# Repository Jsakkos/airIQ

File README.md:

# airQ

Open-source indoor air-quality monitor: ESP32-C6 + Sensirion SEN66 (PM, CO2, VOC, NOx, temperature, humidity), e-paper display, RGB status LED, ESPHome firmware, KiCad PCB and a 3D-printed enclosure.

**Status:** v3 is in design and early implementation.

- Design spec: [docs/superpowers/specs/2026-11-25-airq-v3-design.md](docs/superpowers/specs/2026-11-25-airq-v3-design.md)
- Implementation plans: [docs/superpowers/plans/](docs/superpowers/plans/)
- Research report: [docs/research/reports/Air quality monitor refresh.md](docs/research/reports/Air%20quality%20monitor%20refresh.md)
- Hardware interface contract (GPIOs, I2C addresses, connector pinouts): [hardware/interface.yaml](hardware/interface.yaml)
- Previous generation (v2, ESP8266): [legacy/v2/](legacy/v2/README.md)

## Licences

- `firmware/` and `tools/`: [MIT](LICENSE)
- `hardware/` and `enclosure/`: [CC-BY-SA 4.0](hardware/LICENSE.md)

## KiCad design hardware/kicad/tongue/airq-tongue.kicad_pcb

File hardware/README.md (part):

# airQ v3 hardware

| Path | What |
|---|---|
| `src/<board>/` | **Design source**: the text files the boards are made from (edit these) |
| `kicad/<board>/` | KiCad 10 projects, **generated** from `src/<board>/` (open these, do not edit the schematics) |
| `kicad/lib/` | `airq` symbol, footprint and 3D library ([README](kicad/lib/README.md)) |
| `fab/<board>/` | **JLCPCB upload files**, generated by every build: Gerber + drill zip, `bom.csv`, `cpl.csv` (see "Ordering") |
| `step/` | STEP models of both assembled boards for the enclosure, from `build.py <board> --step` |
| `bom/parts.csv` | LCSC parts table: JLC Economic status, stock, boards |
| `interface.yaml` | GPIOs, I²C addresses and connector pinouts shared with the firmware; board mechanics (`mechanical`) |

Boards: `main` (the main board) and `tongue` (the sense tongue: SHT45 and VEML7700 on a 22 × 13 mm
board cabled to the main board's `J_QWIIC_TONGUE`, see below). Both follow the same scheme.

## Ordering

Both boards are ordered from JLCPCB as PCB + assembly (PCBA). The owner places the orders; nothing in
this repository uploads or orders anything.

**Files to upload, per board** (in `hardware/fab/main/` and `hardware/fab/tongue/`; every build rewrites
them and a test fails if the committed ones differ from a rebuild, see "Fab outputs"):

| File | JLC upload slot | Contents |
|---|---|---|
| `airq-<board>-gerbers.zip` | Gerber file (PCB) | 9 Gerber layers (copper, paste, silkscreen and mask, top and bottom; the outline with the tongue's slot) and the PTH and NPTH Excellon drill files |
| `bom.csv` | BOM (assembly) | `Comment,Designator,Footprint,LCSC`, one line per part kind; DNP parts left out |
| `cpl.csv` | CPL / pick-and-place (assembly) | `Designator,Mid X,Mid Y,Layer,Rotation`, mm from the outline's bottom-left corner, all `Top` |

**JLC options**, the same for both boards:

- PCB: **2 layers, 1.6 mm, lead-free HASL** (FR-4, 1 oz copper). Colour and the rest are the owner's choice.
- Assembly: **Economic** PCBA, top side. The main board has 28 BOM lines, 14 of them Extended parts (≤ 15,
  the fee budget); the tongue 4 lines, 3 Extended. The parts are the owner-confirmed set (2026-11-25):
  ESP32-C6-WROOM-1-N8 (C5366877) and MS5611 (C15639), both Economic-eligible.
- **Prototype round:** fabricate **5**, assemble **2** of each board.
- **Production:** fabricate **10**, assemble **8** of each board.

**Before each order:**

1. Rebuild both boards (`build.py main --routed`, `build.py tongue --routed`: exit 0, DRC clean), run the
   gates and the tests ("Build and check a board" below), and check that `git status` is clean, so the files
   you upload are what was checked. This holds on KiCad 10.0.8, the pinned release: on any other, the
   rebuild rewrites the files KiCad saves (see "Regeneration contract"); check and commit that rebuild first.
2. On the day of the order, look up every BOM part on LCSC/JLC (stock, still "Economic"), update `stock` and
   `checked_on` in `bom/parts.csv`, then run the freshness gate. It must print nothing (exit 0):
   ```
   uv run python tools/hw/check_bom.py hardware/fab/main/bom.csv hardware/bom/parts.csv --fresh-days 7
   uv run python tools/hw/check_bom.py hardware/fab/tongue/bom.csv hardware/bom/parts.csv --fresh-days 7
   ```
   Watch the VEML7700-TR (C504893, tongue): only 308 were in stock on 2026-11-25.
3. **Main boards meant for airQs: test the e-ink extension first.** In the airQ the panel's tail does not
   reach J7, so it connects through a 24-pin adapter and FFC (owner decision 2026-11-26, "E-ink FPC fit
   (airQ)" below). Before ordering main boards for airQs beyond the prototype round, run one prototype airQ
   with the real adapter and FFC: check with a meter, before power, that FPC pin 1 reaches J7 pin 1, then
   confirm full and partial refreshes are clean with the panel's boost (GDR, RESE) running through the
   extension. If either fails, the options in that section are open again. Boards for the bench or the
   airQ mini are not affected.
4. **Side-looking parts, if one of each is at hand:** check against the real part that the SK6812SIDE-A
   emits from the face opposite its terminals (footprint +y, out of the main board's front edge) and that the
   VEML7700-TR's window is on the side opposite its leads (footprint −y, out of the tongue's front edge).
   Both directions were read from 2-D drawings only (`kicad/lib/README.md`, "Pad maps checked by hand", fix 13).
5. After uploading, **look at the files in JLC's Gerber viewer** (every copper, mask, paste and silkscreen
   layer; the outline with the tongue's slot; the drill holes, including the USB-C shell-leg slots and their
   paste) **and check its rotation/offset preview against the silkscreen before paying**: every
   part's pin 1 or polarity mark (D5–D7 cathode bars, the SOT-23 parts U1, U2, U5, Q1, the module U3, U4, and
   the tongue's U1), and the parts that look out of a board edge (LEDs D1–D4, J1–J5, the FPC J7, the button
   SW1, the tongue's VEML7700 U2 and J1) facing out of that edge as the silkscreen shows. The CPL uses
   KiCad's rotations with no per-part offsets (see "Fab outputs"); correct any part JLC shows turned in its
   preview, and note it here for the next order. No Gerber viewer was run on these files before the first
   order; KiCad's own checks and `tests/hardware/test_fab.py` are all that has read them.

**Bought separately** (not on JLC's BOM): 11 SEN66, SEN6x cables (JST GH 6-pin), e-ink panels (GoodDisplay
GDEY029T94), Qwiic cables (JST SH 4-pin, also for the tongue), and the optional SFA40. For each airQ (the
mini needs neither): a 24-pin 0.5 mm FPC adapter and a 24-pin 0.5 mm-pitch FFC for the panel, the FFC's
length and contact sides set by Plan 3's route ("E-ink FPC fit (airQ)" below).

**USB supply and cable** (not part of the BOM, spec §6.7): a 5 V supply good for 1 A and a decent cable. The
TPS562201 buck is specified for VIN ≥ 4.5 V (its undervoltage lockout wakes at 3.8–4.3 V), and the LED buffer
(SN74AHCT1G125, VCC 4.5–5.5 V) runs on +5 V too. A long or thin cable that lets VBUS sag at about 1 A can brown
the board out (ruling R29).

**Not fitted:** J6 (`J_AUX_UART`, DNP): JLC drills and plates its six 2.54 mm holes and fits no header.

**Design rules against JLC's published capabilities** (jlcpcb.com/capabilities/pcb-capabilities and
/pcb-assembly-capabilities, read 2026-11-25; measured with KiCad DRC on both boards):

| Feature | These boards | JLC |
|---|---|---|
| Tongue slot round the SHT45 | 1.0 mm wide, drawn on Edge.Cuts (the GM1 file) | "Min. Non-Plated Slots: 1.0mm", outline in GM1/GKO: **at the minimum, no margin**. JLC may query its square corners ("rectangular holes and slots without rounded corners are not supported"): the router bit rounds them, which is fine here |
| Copper to non-plated holes (M2 holes, SW1 guide holes, USB-C pegs) | ≥ 0.25 mm (SW1 and USB-C pads trimmed, no relaxing DRC rule: `kicad/lib/README.md` fixes 18, 19) | "NPTH to Track: 0.2mm" |
| Copper to plated holes (J6, USB-C shell legs) | ≥ 0.4 mm | "PTH to Track": 0.28 mm minimum, 0.35 mm recommended |
| Annular ring of plated holes | J6 0.35 mm, USB-C shell legs ≥ 0.25 mm | ≥ 0.18 mm absolute minimum, 0.25 mm recommended |
| Vias | 0.6 mm on 0.3 mm; ≥ 0.30 mm from the hole to other copper | 0.25 mm on 0.15 mm minimum; "Via hole to Track: 0.2mm" |
| Track width / clearance | ≥ 0.15 / 0.15 mm | 0.10 / 0.10 mm (1 oz) |
| Copper to the board edge and to the slot | ≥ 0.3 mm | ≥ 0.2 mm from routed edges and slots |
| Board size, assembly | 60 × 30 mm, 22 × 13 mm | Economic PCBA: 10 × 10 mm minimum, one side, 2–50 boards, edge rails and fiducials "not necessary" |
| Silkscreen | text 1.0 mm high, 0.15 mm stroke; some footprint outlines 0.06–0.12 mm (KiCad stock and EasyEDA footprints) | line width ≥ 0.15 mm, text ≥ 1.0 mm high: the thinner outline lines may print faint (cosmetic) |

**Parts at the board edges** (for JLC's question about edge rails, a panel or tabs; Economic PCBA lists edge
rails as not necessary, so adding them is an owner decision on cost). Positions from `interface.yaml`
`mechanical.*`:

| Edge | Parts at or over it |
|---|---|
| Main, rear (y = 0) | the module U3's 6 mm antenna strip **overhangs** it (x 41–59); the USB-C J1's mouth is flush (y 0.03, x 11.7–20.7) |
| Main, front (y = 30) | the LEDs D1–D4 (light faces on the edge), the FPC J7's mouth (on the edge, x 21–36.5), the button SW1's actuator **0.24 mm beyond** it (x 56–58), the J3 and J5 mouths 0.6 and 0.8 mm inside |
| Main, left (x = 0) | the J2 (SEN66) and J4 (Qwiic) mouths, 0.35 and 0.64 mm inside |
| Main, right (x = 60) | nothing; the module body ends 1 mm inside |
| Tongue, front (y = 0) | the VEML7700 U2's window face, 0.25 mm inside (x 14.95–21.75) |
| Tongue, rear (y = 13) | the Qwiic J1's mouth, 0.64 mm inside (x 12–18) |

So the main board's right edge is the only one free of parts, and the only one a rail or V-groove could run
along without touching a part (the module ends 1 mm from it). On the other three edges the parts need their
edge clear: a routed outline with tabs placed away from them, and nothing at all in front of the antenna
strip. On the tongue, keep rails and tabs off the front and rear edges.

The USB-C receptacle J1's four plated shell legs have pin-in-paste apertures on F.Paste, sized to their pads
(`kicad/lib/README.md` fix 22), and reach the pours through thermal reliefs (only its SMD ground pins are
tied solid), so they solder in JLC's SMT reflow with the rest of the part. Still confirm in JLC's review that
the legs get soldered.

### E-ink FPC fit (airQ): decided, extension (option b)

**Decision** (owner, 2026-11-26): option (b) below. A 24-pin 0.5 mm adapter at the panel's tail end takes
the tail, and a 24-pin 0.5 mm FFC runs from it to J7 as placed. **No board change.** In the airQ the tail
folds behind the panel into the adapter. Before ordering airQ boards beyond the prototype round, one
prototype must show the panel's boost (GDR, RESE) working through the extension, and pin 1 arriving on J7
pin 1 (step 3 of "Before each order"). Recorded in `interface.yaml` `mechanical.main.fpc.airq_fit`. The
analysis behind it follows.

**The panel's tail**, read from GoodDisplay's *GDEY029T94 Product Specifications* Rev 1.0 (2021/03/15),
section 4 "Mechanical Drawing of EPD module", p. 7 (front view of the display side, panel landscape, tail on
the left; side view), recorded in `interface.yaml` `mechanical.main.fpc.panel_tail`. "Upper" and "lower"
are as in that view:

- It leaves one **short (36.7 mm) end** of the 79.0 × 36.7 mm outline, flat, in the panel's plane.
- It is **14.40 mm long** from the outline to the finger end, and **12.50 mm wide** over the 9.56 mm next to
  the finger end. There its edges are 11.50 mm from the lower long edge and 12.70 mm from the upper, so its
  centre is 0.60 mm off the centre of that end.
- It then flares and reaches its full **15.31 mm** 11.98 mm from the finger end, so the last 2.42 mm before
  the outline (the root) is full width. The root's edges are 10.97 mm from the lower long edge and 10.42 mm
  from the upper.
- Its 24 contacts (0.5 mm pitch, 3.66 mm long) are on the display side. A 6.20 mm stiffener is on the back,
  from the finger end (the tail is 0.3 mm thick there), so only the 8.2 mm next to the glass can bend.
- Seen from the display side with the tail on the left, **pin 1 is the upper contact**, on the side of the
  long edge 12.70 mm away; pin 24 is the lower one.
- An unlabelled hatched block at that end, about 2.3–7.4 mm from the pin-1 long edge, reaches about 4.6 mm
  past the outline (scaled from the drawing). Check it on a real panel before sizing the panel pocket.

**Reach: not reachable as placed.** The assumed airQ pose (spec §6.4, §6.9):

- The panel is landscape on the front face, display toward the user, tilted 30° back and centred over the
  board's width (x 30).
- The board is horizontal below it, its front edge just behind the front face.
- The panel's lower edge is at or above the board's top face (the LED line is under the screen).
- **The tail folds behind the panel.** The airQ is 95 mm wide outside, about 91 mm inside. The panel's
  79.0 mm plus a flat 14.4 mm tail is 93.4 mm, so wherever the panel sits the tail cannot stay flat in its
  plane: it folds 180° behind the panel (within the 8.2 mm that can bend), and the adapter sits there.

J7 takes the tail through its mouth on the front edge (x 22.55–35.05 for the 12.5 mm tail, about 1 mm above
the board), travelling −Y. The rest is geometry, with a zero bend radius:

- **Distance** (figures for the tail on the user's left; in brackets, on the right, with the panel turned
  180°). The tail's root is at the panel's end, x −9.5 (69.5), 9.5 mm beyond the board's side edge. Its
  lowest corner is 10.97 (10.42) mm up the tilted panel, so 9.50 (9.02) mm above the board. From that corner
  to the nearest end of J7's slot is about 33.6 (35.8) mm in a straight line, and about 3.5 mm more goes
  inside the connector. That needs about 37.1 (39.3) mm of tail. There are 14.4 mm: **about 22.7 (24.9) mm
  short**, before any fold. The exact pose moves this by a few tenths of a millimetre; the horizontal gap
  alone makes it at least 21.1 (23.5) mm.
- **Direction.** The tail leaves along ±X with its width running up the panel. J7 needs it travelling −Y,
  with its width along X and lying flat. That takes a diagonal (45°) crease and a bend, or a twist, and each
  uses up more length.
- **Moving J7 alone does not help.** The root is 9.5 mm beyond the board's side edges (the panel is 79 mm
  wide, the board 60), so no J7 on the board sits under it. Even with J7 at the board's left end, the
  straight line from the root's lowest corner to its slot is about 15 mm, plus 3.5 mm inside J7: about
  18.5 mm against the tail's 14.4, before the direction change and the fold behind the panel.

**Pin 1, whatever the route.** Folds and twists turn the tail but never mirror it. The order in J7 therefore
depends only on which face of the tail is up inside J7:

- **contacts (display side) up:** FPC pin *i* lands on J7 pin *i*, as on the bench (panel flat, display up,
  tail pointing straight into J7; `kicad/lib/README.md` R27);
- **contacts down:** mirrored, FPC pin 1 on J7 pin 24.

For example, a tail folded 180° behind the panel and then turned down into J7 arrives contacts down, so it is
mirrored. Taken one at a time: a 180° fold keeps the tail's edges where they are but turns its face over, and
a twist about its axis swaps the edges and turns the face over.

**Options** (the owner chose (b) on 2026-11-26; the layout is unchanged):

- **(a) Move J7 toward the panel's tail end** (the left or right board edge). Not enough on its own (above).
  It helps only with (b), where it shortens the extension. Not taken.
- **(b) Extension. Chosen.** A 24-pin 0.5 mm adapter at the panel's tail end takes the tail, and a 24-pin
  0.5 mm FFC runs from it to J7 as placed.
  - No board change. J7's contacts are on both sides, so either FFC face mates; the route sets the order (the
    rule above, applied to the FFC), and a 180° twist in the FFC's free span corrects a mirrored arrival.
  - In the airQ the adapter sits behind the panel, and the tail's 180° fold into it turns the tail's face
    over (the rule above). Plan 3 routes the FFC from there to J7 and sets its length and contact sides.
  - Costs: an adapter and an FFC per airQ (the mini needs neither); see "Bought separately".
  - Risks: the panel's boost gate drive (GDR) and current sense (RESE) run through the extension. **Test it
    on the prototype before ordering airQ boards beyond the prototype round** (step 3 of "Before each
    order"). The FFC enters at the front edge between D2 and D3, in the strip the light guide needs too
    (Plan 3).
- **(c) A panel whose tail reaches J7:** a longer tail, or one leaving a long edge. None is known. The spec's
  other candidate, the Waveshare 2.9″ V2 raw panel, was not measured here.

The prototype round is not affected: on the bench the panel lies flat, display up, with its tail straight
into J7 (1:1).

## Toolchain

### Route: an in-repo generator (route c)

The boards are written as YAML in `hardware/src/<board>/`. A small Python generator in `tools/hw/` turns
them into a native KiCad 10 project (hierarchical schematic, board, project settings, library tables), then
runs `kicad-cli` for ERC, DRC, netlist, JLC BOM/CPL, and KiCad's bundled Python for the Specctra DSN.

Why this route: of the three candidates of the plan, it is the only one that passes all five criteria
on this machine without a system change.

| Criterion | How it is met |
|---|---|
| 1. Diffable source the assistant edits reliably | Short YAML files: parts, their pins → net names, page and board positions. The generator rejects unknown keys, pins without a net, off-grid or touching pins with one message per problem. |
| 2. Native KiCad 10 schematic **and** board | KiCad itself saves the schematic sheets and the board (`kicad-cli sch/pcb upgrade --force`, then DRC's `--save-board`), so those files are in KiCad 10.0's own format. The project's library tables resolve every symbol and footprint. |
| 3. ERC and DRC with `kicad-cli` | `kicad-cli sch erc` and `kicad-cli pcb drc --schematic-parity` run on the generated project. |
| 4. JLC BOM and CPL with LCSC numbers | Every part carries an `LCSC` field. `kicad-cli sch export bom` writes JLC's columns, and `pcb export pos` gives the CPL (`tools/hw/jlc.py`). |
| 5. Runs on this Windows machine | Plain Python (uv) + KiCad 10 for Windows. No WSL. |

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
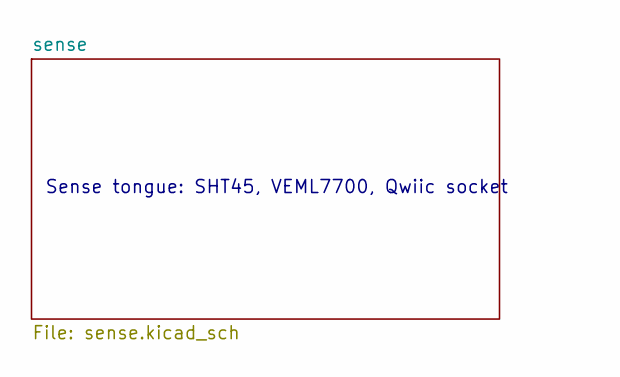
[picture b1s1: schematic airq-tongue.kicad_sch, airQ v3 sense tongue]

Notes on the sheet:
Sense tongue: SHT45, VEML7700, Qwiic socket

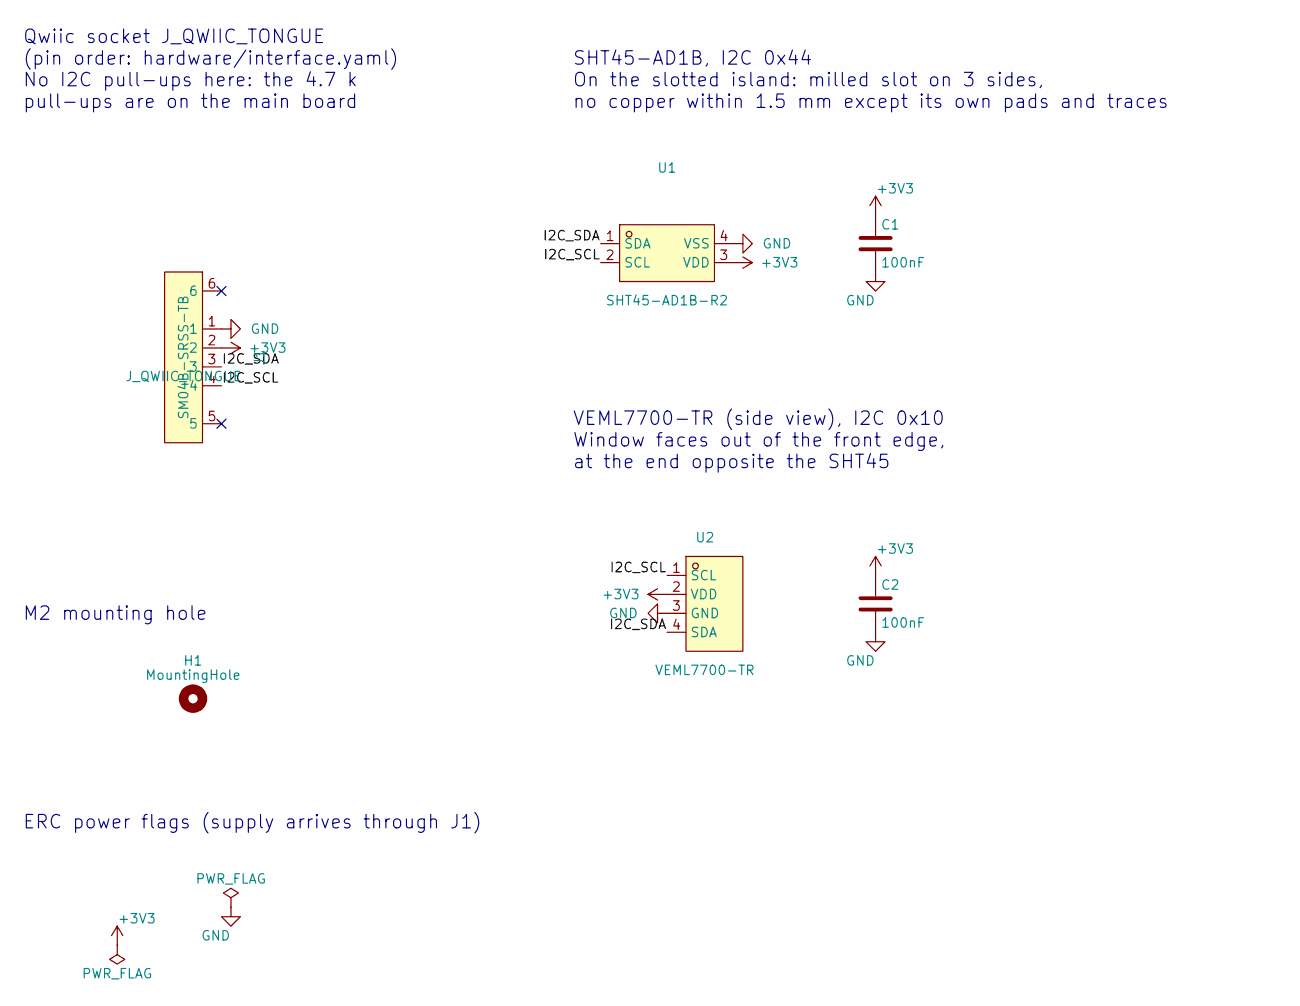
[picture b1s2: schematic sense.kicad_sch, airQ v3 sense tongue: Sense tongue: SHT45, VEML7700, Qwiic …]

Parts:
C1, C2: 100nF; C_0402_1005Metric; LCSC C1525
H1: MountingHole; MountingHole_2.2mm_M2
J1: SM04B-SRSS-TB; CONN-SMD_4P-P1.00_SM04B-SRSS-TB-LF-SN; MPN SM04B-SRSS-TB(LF)(SN); LCSC C160404
U1: SHT45-AD1B-R2; DFN-4_L1.5-W1.5-P0.8-TL-EP; MPN SHT45-AD1B-R2; LCSC C5221601
U2: VEML7700-TR; LED-SMD_4P-L6.8-W2.4_VEML7700-TR; MPN VEML7700-TR; LCSC C504893

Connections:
+3V3: C1.1, C2.1, J1.2, U1.3 (VDD), U2.2 (VDD)
/sense/I2C_SCL: J1.4, U1.2 (SCL), U2.1 (SCL)
/sense/I2C_SDA: J1.3, U1.1 (SDA), U2.4 (SDA)
GND: C1.2, C2.2, J1.1, U1.4 (VSS), U2.3 (GND)

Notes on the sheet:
SHT45-AD1B, I2C 0x44 On the slotted island: milled slot on 3 sides, no copper within 1.5 mm except its own pads and traces
M2 mounting hole
VEML7700-TR (side view), I2C 0x10 Window faces out of the front edge, at the end opposite the SHT45
Qwiic socket J_QWIIC_TONGUE (pin order: hardware/interface.yaml) No I2C pull-ups here: the 4.7 k pull-ups are on the main board
ERC power flags (supply arrives through J1)

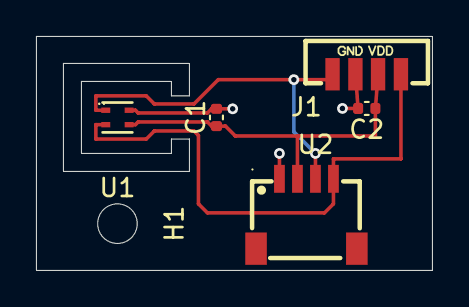
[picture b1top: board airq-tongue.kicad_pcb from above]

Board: 2 copper layers, 22.0 x 13.0 mm, 6 parts (0 on the bottom side), 4 nets.

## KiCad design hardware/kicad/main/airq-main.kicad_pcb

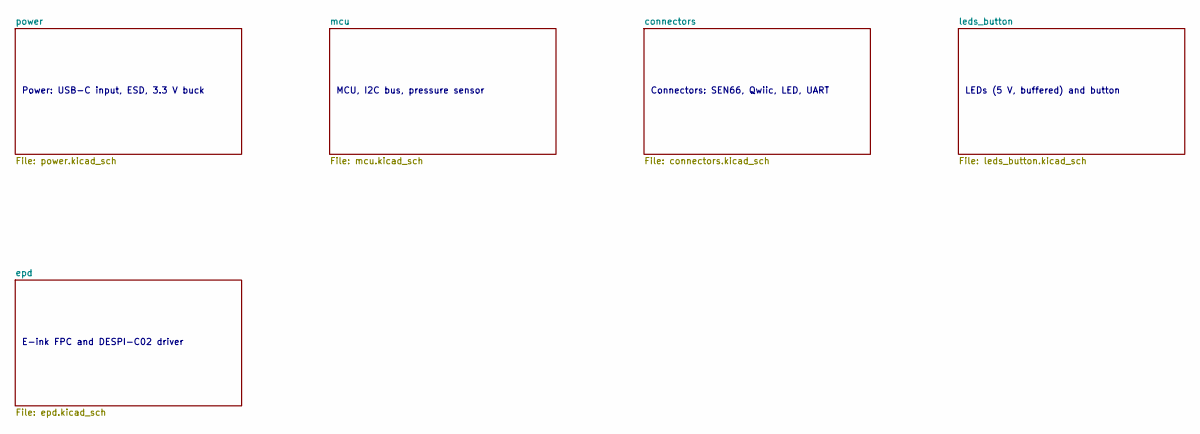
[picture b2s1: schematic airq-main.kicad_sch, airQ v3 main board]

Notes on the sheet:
MCU, I2C bus, pressure sensor
E-ink FPC and DESPI-C02 driver
Connectors: SEN66, Qwiic, LED, UART
Power: USB-C input, ESD, 3.3 V buck
LEDs (5 V, buffered) and button

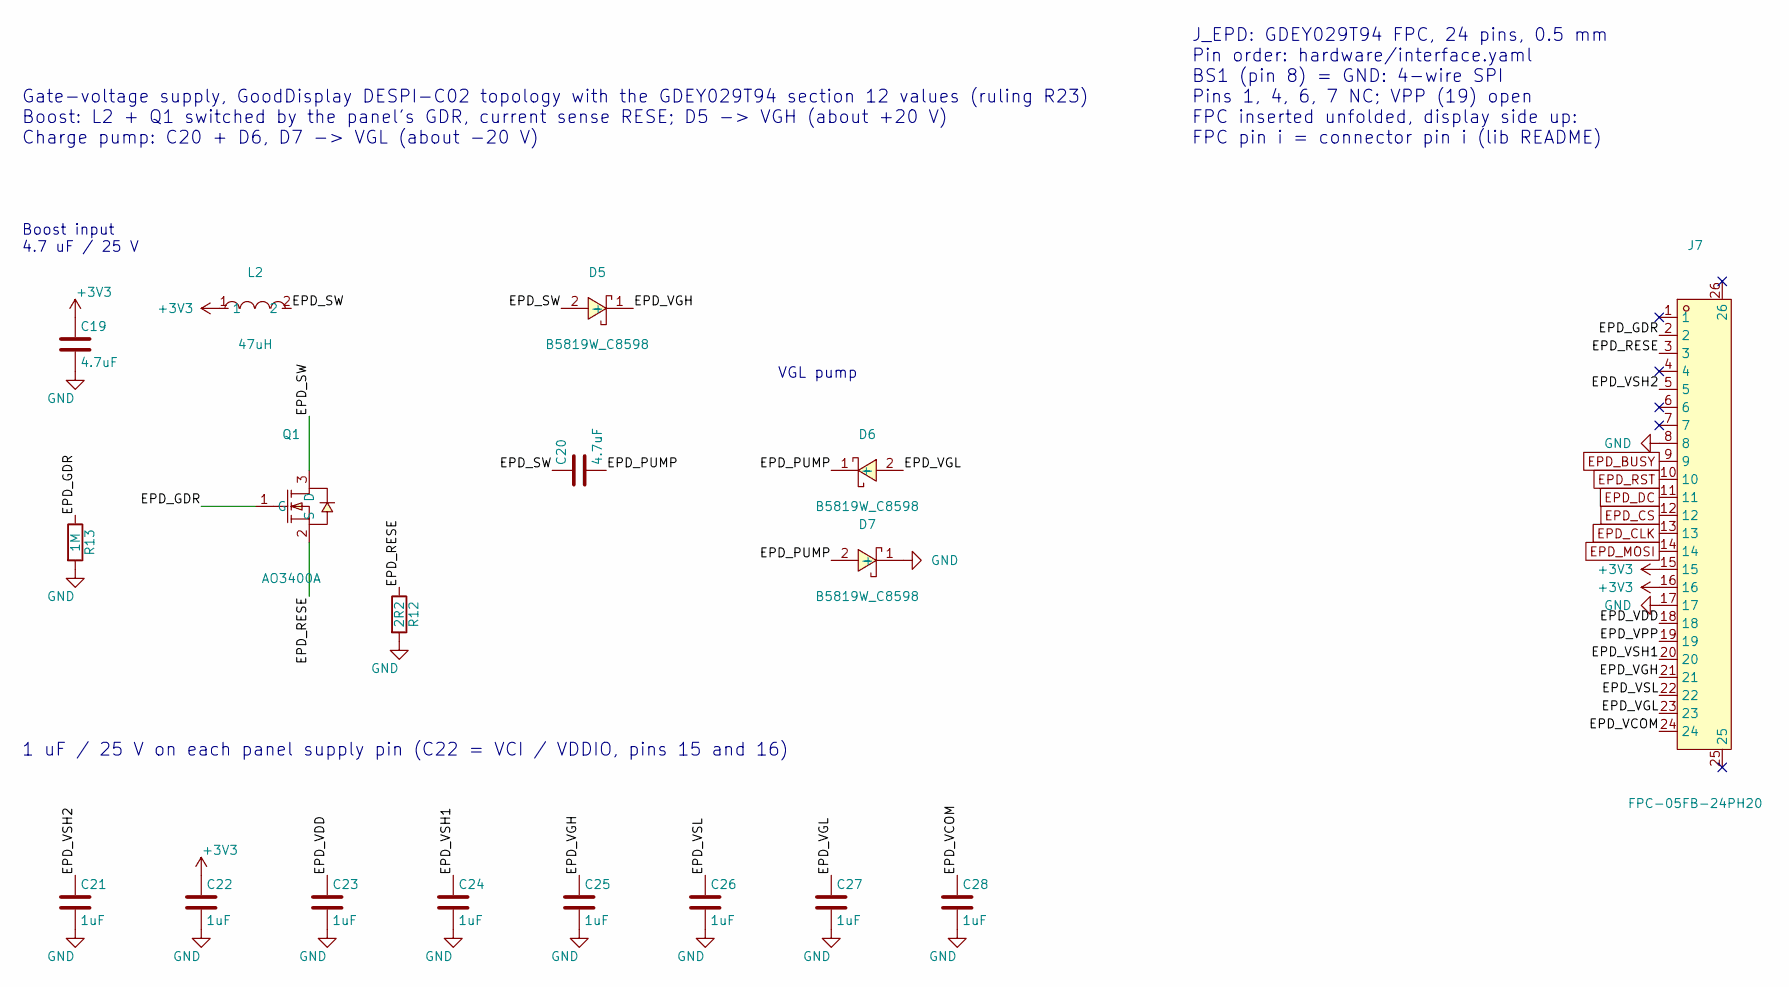
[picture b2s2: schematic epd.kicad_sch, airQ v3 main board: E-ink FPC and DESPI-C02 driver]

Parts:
C19, C20: 4.7uF; C_0805_2012Metric; LCSC C1779
C21, C22, C23, C24, C25, C26, C27, C28: 1uF; C_0603_1608Metric; LCSC C15849
D5, D6, D7: B5819W_C8598; SOD-123_L2.7-W1.6-LS3.7-RD-1; MPN B5819W SL; LCSC C8598
J7: FPC-05FB-24PH20; FPC-SMD_24P-P0.50_FPC-05FB-24PH20; MPN FPC-05FB-24PH20; LCSC C2856831
L2: 47uH; IND-SMD_L4.0-W4.0_SMNR4020; MPN SMNR4030-470MT; LCSC C135276
Q1: AO3400A; SOT-23-3_L2.9-W1.3-P1.90-LS2.4-BR; MPN AO3400A; LCSC C20917
R12: 2R2; R_0603_1608Metric; LCSC C22939
R13: 1M; R_0603_1608Metric; LCSC C22935

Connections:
+3V3: C19.1, C22.1, J7.15, J7.16, L2.1; also elsewhere on the board
/epd/EPD_GDR: J7.2, Q1.1 (G), R13.1
/epd/EPD_PUMP: C20.2, D6.1 (-), D7.2 (+)
/epd/EPD_RESE: J7.3, Q1.2 (S), R12.1
/epd/EPD_SW: C20.1, D5.2 (+), L2.2, Q1.3 (D)
/epd/EPD_VCOM: C28.1, J7.24
/epd/EPD_VDD: C23.1, J7.18
/epd/EPD_VGH: C25.1, D5.1 (-), J7.21
/epd/EPD_VGL: C27.1, D6.2 (+), J7.23
/epd/EPD_VPP: J7.19
/epd/EPD_VSH1: C24.1, J7.20
/epd/EPD_VSH2: C21.1, J7.5
/epd/EPD_VSL: C26.1, J7.22
EPD_BUSY: J7.9; also elsewhere on the board
EPD_CLK: J7.13; also elsewhere on the board
EPD_CS: J7.12; also elsewhere on the board
EPD_DC: J7.11; also elsewhere on the board
EPD_MOSI: J7.14; also elsewhere on the board
EPD_RST: J7.10; also elsewhere on the board
GND: C19.2, C21.2, C22.2, C23.2, C24.2, C25.2, C26.2, C27.2, C28.2, D7.1 (-), J7.8, J7.17, R12.2, R13.2; also elsewhere on the board

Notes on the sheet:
VGL pump
Boost input 4.7 uF / 25 V
1 uF / 25 V on each panel supply pin (C22 = VCI / VDDIO, pins 15 and 16)
Gate-voltage supply, GoodDisplay DESPI-C02 topology with the GDEY029T94 section 12 values (ruling R23) Boost: L2 + Q1 switched by the panel's GDR, current sense RESE; D5 -> VGH (about +20 V) Charge pump: C20 + D6, D7 -> VGL (about -20 V)
J_EPD: GDEY029T94 FPC, 24 pins, 0.5 mm Pin order: hardware/interface.yaml BS1 (pin 8) = GND: 4-wire SPI Pins 1, 4, 6, 7 NC; VPP (19) open FPC inserted unfolded, display side up: FPC pin i = connector pin i (lib README)

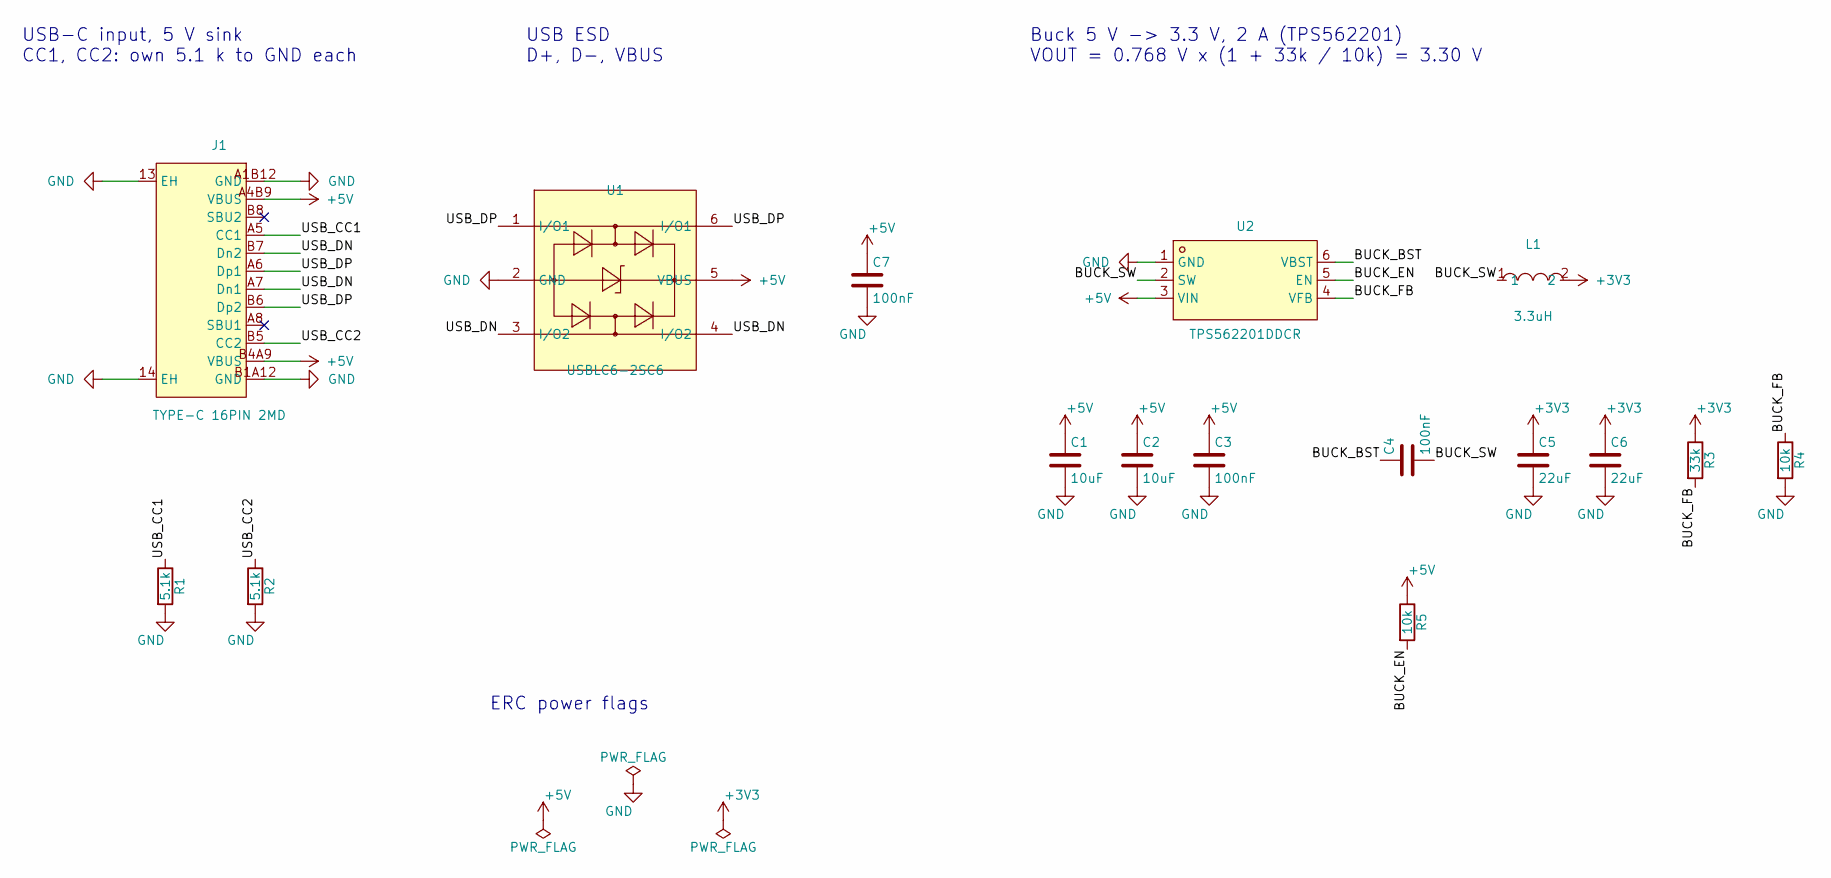
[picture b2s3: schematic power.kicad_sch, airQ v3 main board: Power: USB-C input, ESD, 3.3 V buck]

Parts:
C1, C2: 10uF; C_0805_2012Metric; LCSC C15850
C3, C4, C7: 100nF; C_0402_1005Metric; LCSC C1525
C5, C6: 22uF; C_0805_2012Metric; LCSC C45783
J1: TYPE-C 16PIN 2MD; USB-C-SMD_TYPE-C-16PIN-2MD-073; MPN TYPE-C 16PIN 2MD(073); LCSC C2765186
L1: 3.3uH; IND-SMD_L4.0-W4.0_WPN4020H; MPN WPN4020H3R3MT; LCSC C98362
R1, R2: 5.1k; R_0402_1005Metric; LCSC C25905
R3: 33k; R_0402_1005Metric; LCSC C25779
R4, R5: 10k; R_0402_1005Metric; LCSC C25744
U1: USBLC6-2SC6; SOT-23-6_L2.9-W1.6-P0.95-LS2.8-BL; MPN USBLC6-2SC6; LCSC C7519
U2: TPS562201DDCR; SOT-23-6_L2.9-W1.6-P0.95-LS2.8-BR; MPN TPS562201DDCR; LCSC C90061

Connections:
+3V3: C5.1, C6.1, L1.2, R3.1; also elsewhere on the board
+5V: C1.1, C2.1, C3.1, C7.1, J1.A4B9 (VBUS), J1.B4A9 (VBUS), R5.1, U1.5 (VBUS), U2.3 (VIN); also elsewhere on the board
/power/BUCK_BST: C4.1, U2.6 (VBST)
/power/BUCK_EN: R5.2, U2.5 (EN)
/power/BUCK_FB: R3.2, R4.1, U2.4 (VFB)
/power/BUCK_SW: C4.2, L1.1, U2.2 (SW)
/power/USB_CC1: J1.A5 (CC1), R1.1
/power/USB_CC2: J1.B5 (CC2), R2.1
GND: C1.2, C2.2, C3.2, C5.2, C6.2, C7.2, J1.13 (EH), J1.14 (EH), J1.A1B12 (GND), J1.B1A12 (GND), R1.2, R2.2, R4.2, U1.2 (GND), U2.1 (GND); also elsewhere on the board
USB_DN: J1.A7 (Dn1), J1.B7 (Dn2), U1.3 (I/O2), U1.4 (I/O2); also elsewhere on the board
USB_DP: J1.A6 (Dp1), J1.B6 (Dp2), U1.1 (I/O1), U1.6 (I/O1); also elsewhere on the board

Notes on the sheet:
USB-C input, 5 V sink CC1, CC2: own 5.1 k to GND each
Buck 5 V -> 3.3 V, 2 A (TPS562201) VOUT = 0.768 V x (1 + 33k / 10k) = 3.30 V
ERC power flags
USB ESD D+, D-, VBUS

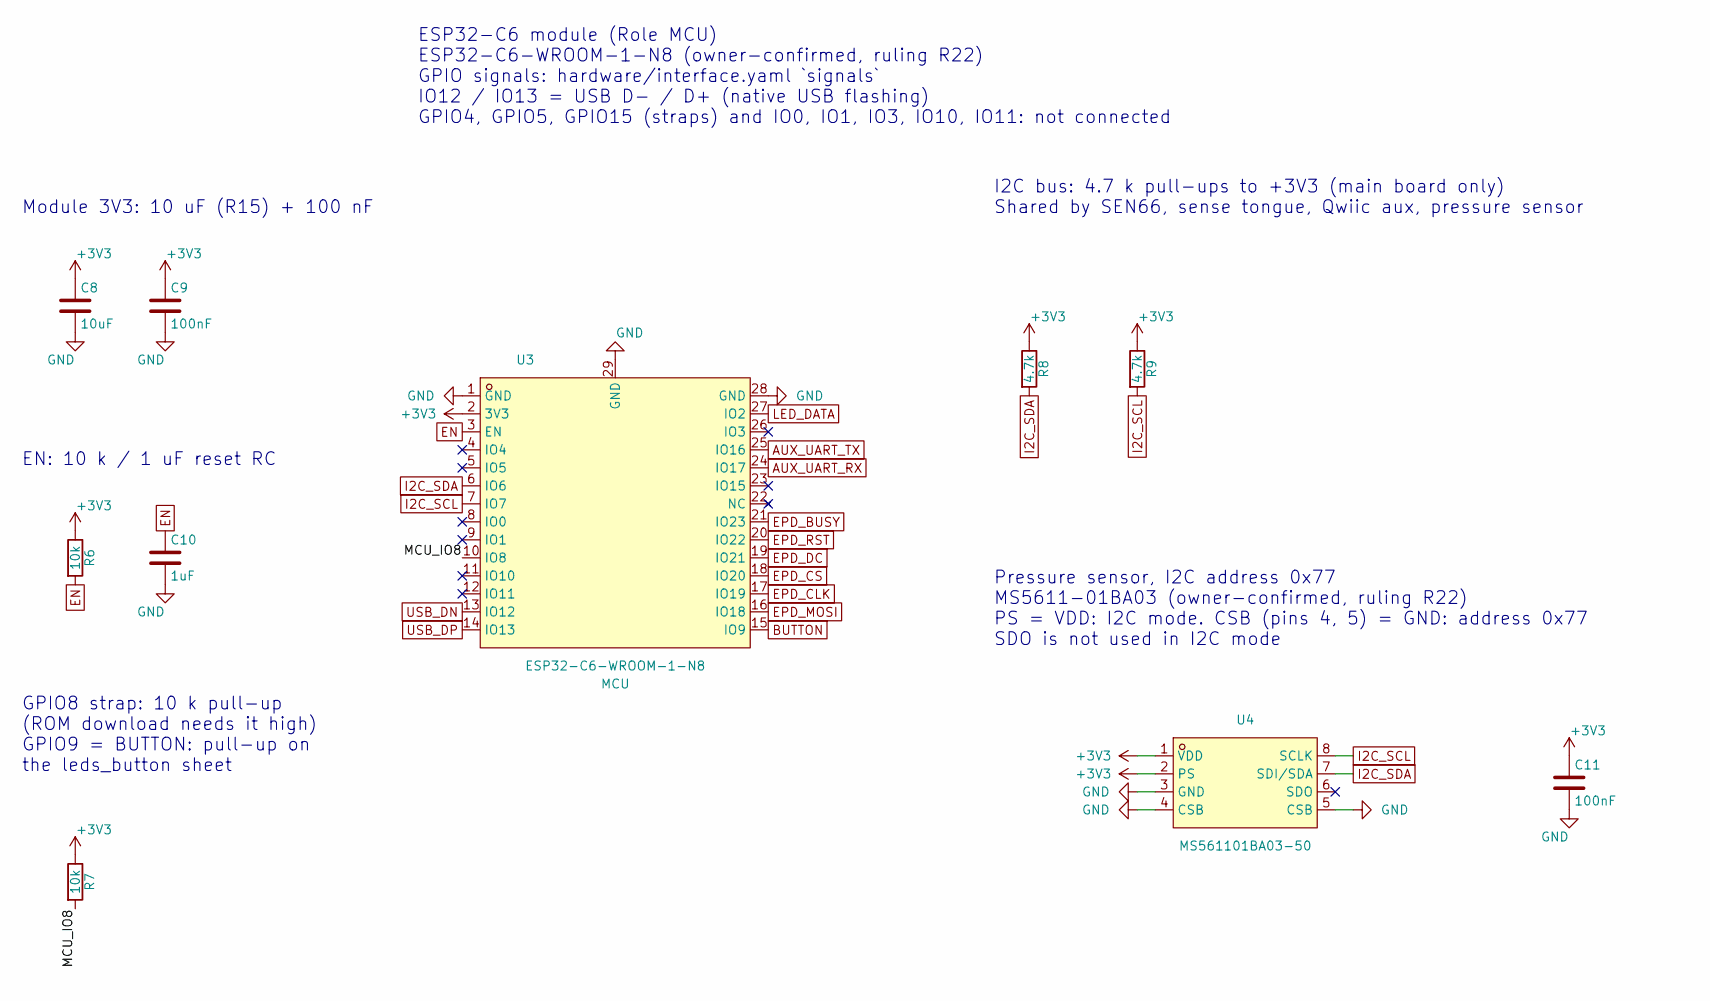
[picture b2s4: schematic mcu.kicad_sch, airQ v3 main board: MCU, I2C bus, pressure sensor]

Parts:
C8: 10uF; C_0805_2012Metric; LCSC C15850
C9, C11: 100nF; C_0402_1005Metric; LCSC C1525
C10: 1uF; C_0603_1608Metric; LCSC C15849
R6, R7: 10k; R_0402_1005Metric; LCSC C25744
R8, R9: 4.7k; R_0402_1005Metric; LCSC C25900
U3: ESP32-C6-WROOM-1-N8; WIRELM-SMD_ESP32-C6-WROOM-1; MPN ESP32-C6-WROOM-1-N8; LCSC C5366877
U4: MS561101BA03-50; SENSORS-SMD_MS5611-01BA03; MPN MS561101BA03-50; LCSC C15639

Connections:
+3V3: C8.1, C9.1, C11.1, R6.1, R7.1, R8.1, R9.1, U3.2 (3V3), U4.1 (VDD), U4.2 (PS); also elsewhere on the board
/mcu/MCU_IO8: R7.2, U3.10 (IO8)
AUX_UART_RX: U3.24 (IO17); also elsewhere on the board
AUX_UART_TX: U3.25 (IO16); also elsewhere on the board
BUTTON: U3.15 (IO9); also elsewhere on the board
EN: C10.1, R6.2, U3.3 (EN); also elsewhere on the board
EPD_BUSY: U3.21 (IO23); also elsewhere on the board
EPD_CLK: U3.17 (IO19); also elsewhere on the board
EPD_CS: U3.18 (IO20); also elsewhere on the board
EPD_DC: U3.19 (IO21); also elsewhere on the board
EPD_MOSI: U3.16 (IO18); also elsewhere on the board
EPD_RST: U3.20 (IO22); also elsewhere on the board
GND: C8.2, C9.2, C10.2, C11.2, U3.1 (GND), U3.28 (GND), U3.29 (GND), U3.30 (GND), U3.31 (GND), U3.32 (GND), U3.33 (GND), U3.34 (GND), U3.35 (GND), U3.36 (GND), U3.37 (GND), U4.3 (GND), U4.4 (CSB), U4.5 (CSB); also elsewhere on the board
I2C_SCL: R9.2, U3.7 (IO7), U4.8 (SCLK); also elsewhere on the board
I2C_SDA: R8.2, U3.6 (IO6), U4.7 (SDI/SDA); also elsewhere on the board
LED_DATA: U3.27 (IO2); also elsewhere on the board
USB_DN: U3.13 (IO12); also elsewhere on the board
USB_DP: U3.14 (IO13); also elsewhere on the board

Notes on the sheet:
Module 3V3: 10 uF (R15) + 100 nF
ESP32-C6 module (Role MCU) ESP32-C6-WROOM-1-N8 (owner-confirmed, ruling R22) GPIO signals: hardware/interface.yaml `signals` IO12 / IO13 = USB D- / D+ (native USB flashing) GPIO4, GPIO5, GPIO15 (straps) and IO0, IO1, IO3, IO10, IO11: not connected
Pressure sensor, I2C address 0x77 MS5611-01BA03 (owner-confirmed, ruling R22) PS = VDD: I2C mode. CSB (pins 4, 5) = GND: address 0x77 SDO is not used in I2C mode
GPIO8 strap: 10 k pull-up (ROM download needs it high) GPIO9 = BUTTON: pull-up on the leds_button sheet
EN: 10 k / 1 uF reset RC
I2C bus: 4.7 k pull-ups to +3V3 (main board only) Shared by SEN66, sense tongue, Qwiic aux, pressure sensor

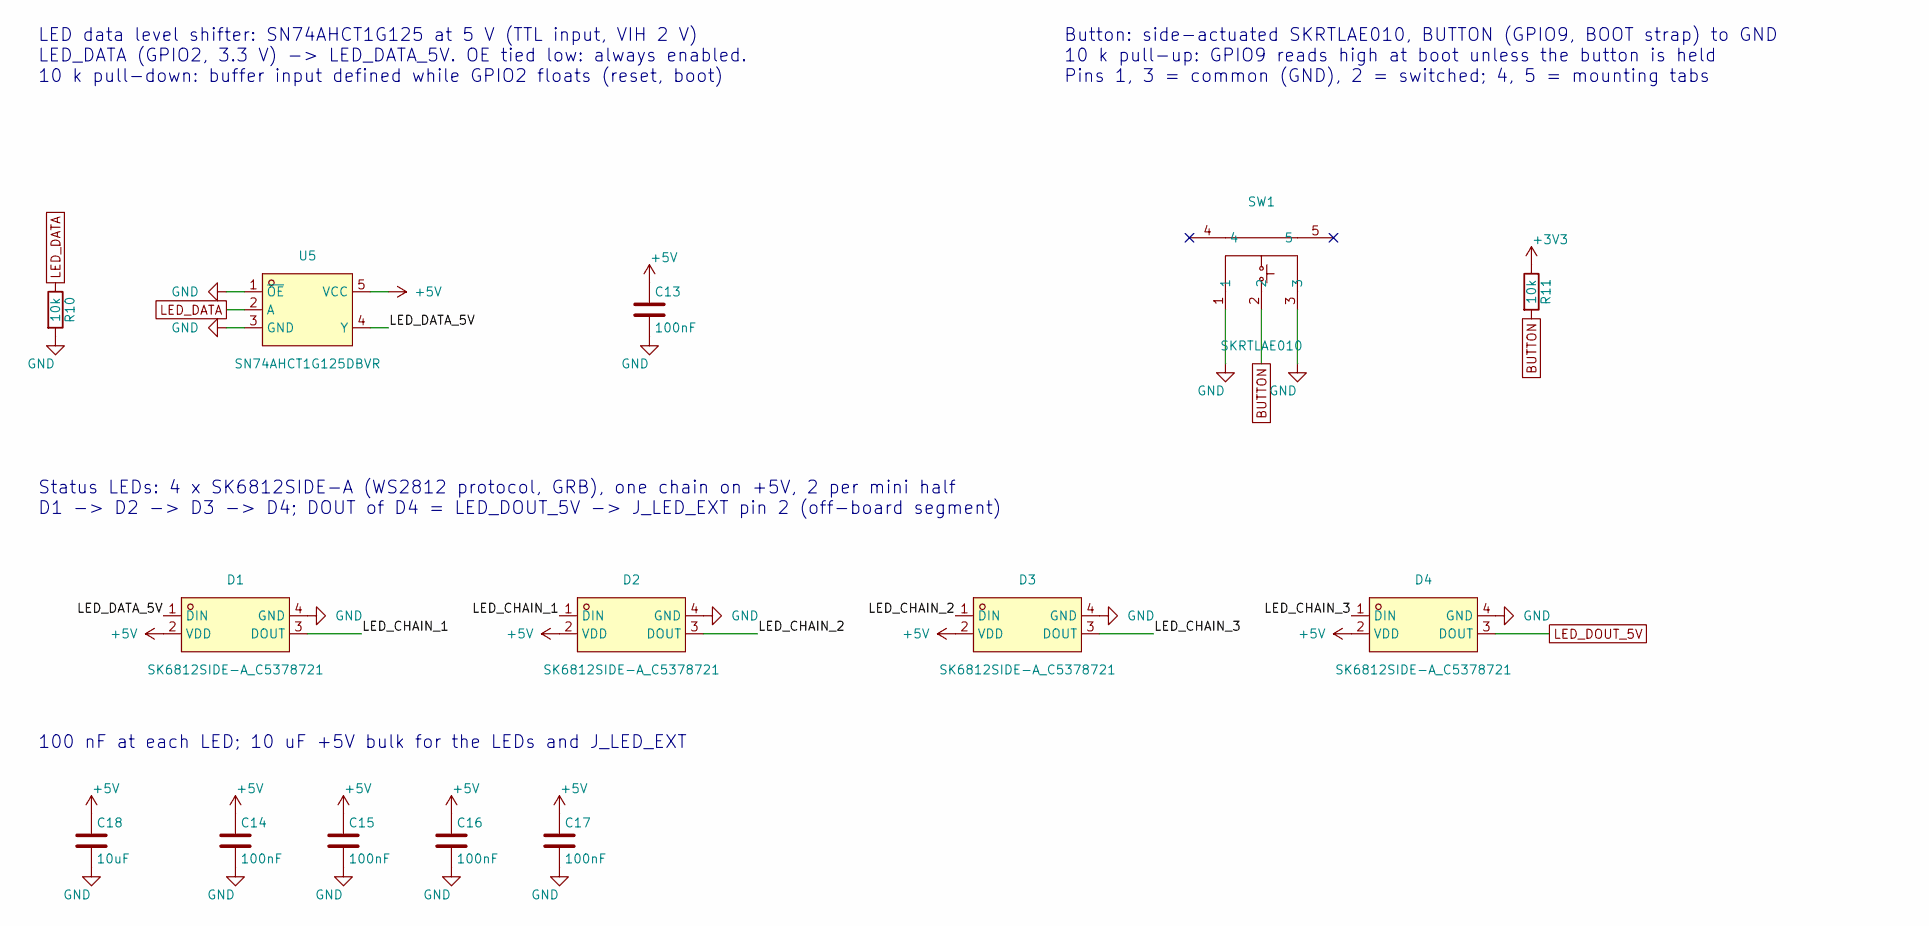
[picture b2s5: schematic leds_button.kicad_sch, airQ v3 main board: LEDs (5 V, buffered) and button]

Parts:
C13, C14, C15, C16, C17: 100nF; C_0402_1005Metric; LCSC C1525
C18: 10uF; C_0805_2012Metric; LCSC C15850
D1, D2, D3, D4: SK6812SIDE-A_C5378721; LED-SMD_4P-L4.0-W1.6-L; MPN SK6812SIDE-A; LCSC C5378721
R10, R11: 10k; R_0402_1005Metric; LCSC C25744
SW1: SKRTLAE010; KEY-SMD_SKRTLAE010; MPN SKRTLAE010; LCSC C110293
U5: SN74AHCT1G125DBVR; SOT-23-5_L3.0-W1.7-P0.95-LS2.8-BR; MPN SN74AHCT1G125DBVR; LCSC C7484

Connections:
+3V3: R11.1; also elsewhere on the board
+5V: C13.1, C14.1, C15.1, C16.1, C17.1, C18.1, D1.2 (VDD), D2.2 (VDD), D3.2 (VDD), D4.2 (VDD), U5.5 (VCC); also elsewhere on the board
/leds_button/LED_CHAIN_1: D1.3 (DOUT), D2.1 (DIN)
/leds_button/LED_CHAIN_2: D2.3 (DOUT), D3.1 (DIN)
/leds_button/LED_CHAIN_3: D3.3 (DOUT), D4.1 (DIN)
BUTTON: R11.2, SW1.2; also elsewhere on the board
GND: C13.2, C14.2, C15.2, C16.2, C17.2, C18.2, D1.4 (GND), D2.4 (GND), D3.4 (GND), D4.4 (GND), R10.2, SW1.1, SW1.3, U5.1 (~OE), U5.3 (GND); also elsewhere on the board
LED_DATA: R10.1, U5.2 (A); also elsewhere on the board
LED_DOUT_5V: D4.3 (DOUT); also elsewhere on the board

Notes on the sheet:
LED data level shifter: SN74AHCT1G125 at 5 V (TTL input, VIH 2 V) LED_DATA (GPIO2, 3.3 V) -> LED_DATA_5V. OE tied low: always enabled. 10 k pull-down: buffer input defined while GPIO2 floats (reset, boot)
100 nF at each LED; 10 uF +5V bulk for the LEDs and J_LED_EXT
Status LEDs: 4 x SK6812SIDE-A (WS2812 protocol, GRB), one chain on +5V, 2 per mini half D1 -> D2 -> D3 -> D4; DOUT of D4 = LED_DOUT_5V -> J_LED_EXT pin 2 (off-board segment)
Button: side-actuated SKRTLAE010, BUTTON (GPIO9, BOOT strap) to GND 10 k pull-up: GPIO9 reads high at boot unless the button is held Pins 1, 3 = common (GND), 2 = switched; 4, 5 = mounting tabs

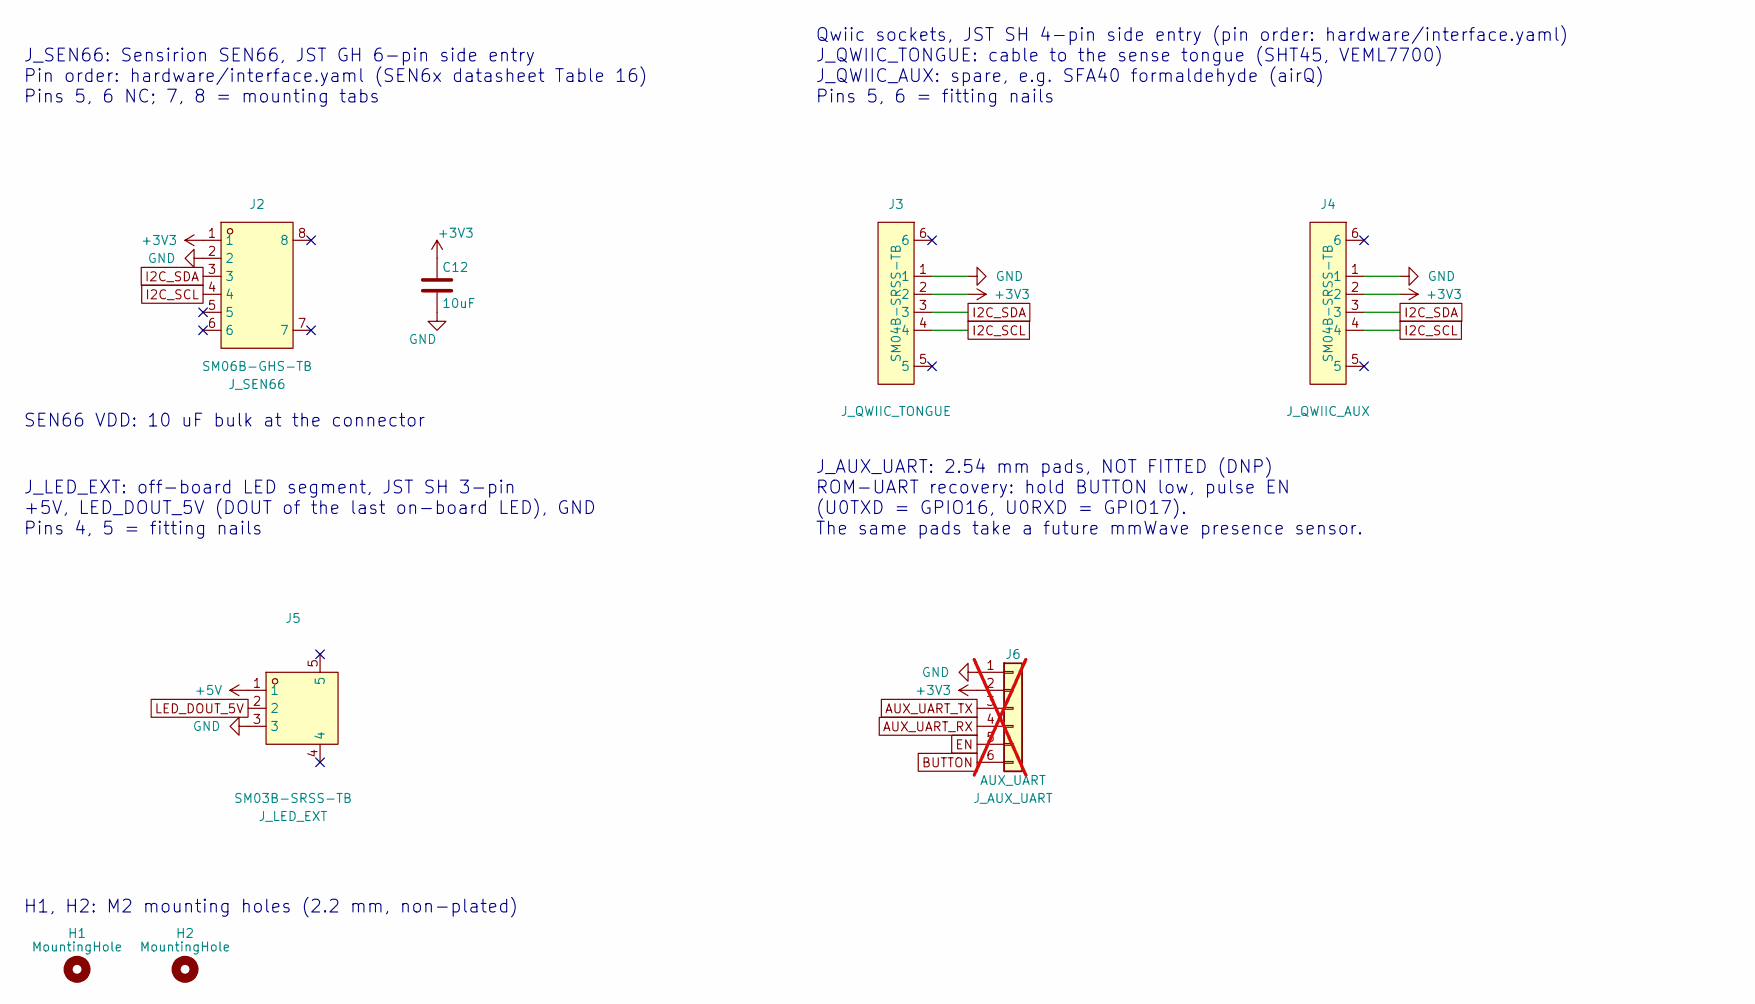
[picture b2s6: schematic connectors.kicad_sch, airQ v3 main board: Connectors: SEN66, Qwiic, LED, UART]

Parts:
C12: 10uF; C_0805_2012Metric; LCSC C15850
H1, H2: MountingHole; MountingHole_2.2mm_M2
J2: SM06B-GHS-TB; CONN-TH_SM06B-GHS-TB-LF-SN; MPN SM06B-GHS-TB(LF)(SN); LCSC C133065
J3, J4: SM04B-SRSS-TB; CONN-SMD_4P-P1.00_SM04B-SRSS-TB-LF-SN; MPN SM04B-SRSS-TB(LF)(SN); LCSC C160404
J5: SM03B-SRSS-TB; CONN-SMD_SM03B-SRSS-TB-LF-SN-P; MPN SM03B-SRSS-TB(LF)(SN); LCSC C160403
J6: AUX_UART; PinHeader_1x06_P2.54mm_Vertical; not fitted

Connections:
+3V3: C12.1, J2.1, J3.2, J4.2, J6.2; also elsewhere on the board
+5V: J5.1; also elsewhere on the board
AUX_UART_RX: J6.4; also elsewhere on the board
AUX_UART_TX: J6.3; also elsewhere on the board
BUTTON: J6.6; also elsewhere on the board
EN: J6.5; also elsewhere on the board
GND: C12.2, J2.2, J3.1, J4.1, J5.3, J6.1; also elsewhere on the board
I2C_SCL: J2.4, J3.4, J4.4; also elsewhere on the board
I2C_SDA: J2.3, J3.3, J4.3; also elsewhere on the board
LED_DOUT_5V: J5.2; also elsewhere on the board

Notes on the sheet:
J_LED_EXT: off-board LED segment, JST SH 3-pin +5V, LED_DOUT_5V (DOUT of the last on-board LED), GND Pins 4, 5 = fitting nails
J_AUX_UART: 2.54 mm pads, NOT FITTED (DNP) ROM-UART recovery: hold BUTTON low, pulse EN (U0TXD = GPIO16, U0RXD = GPIO17). The same pads take a future mmWave presence sensor.
Qwiic sockets, JST SH 4-pin side entry (pin order: hardware/interface.yaml) J_QWIIC_TONGUE: cable to the sense tongue (SHT45, VEML7700) J_QWIIC_AUX: spare, e.g. SFA40 formaldehyde (airQ) Pins 5, 6 = fitting nails
H1, H2: M2 mounting holes (2.2 mm, non-plated)
J_SEN66: Sensirion SEN66, JST GH 6-pin side entry Pin order: hardware/interface.yaml (SEN6x datasheet Table 16) Pins 5, 6 NC; 7, 8 = mounting tabs
SEN66 VDD: 10 uF bulk at the connector

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
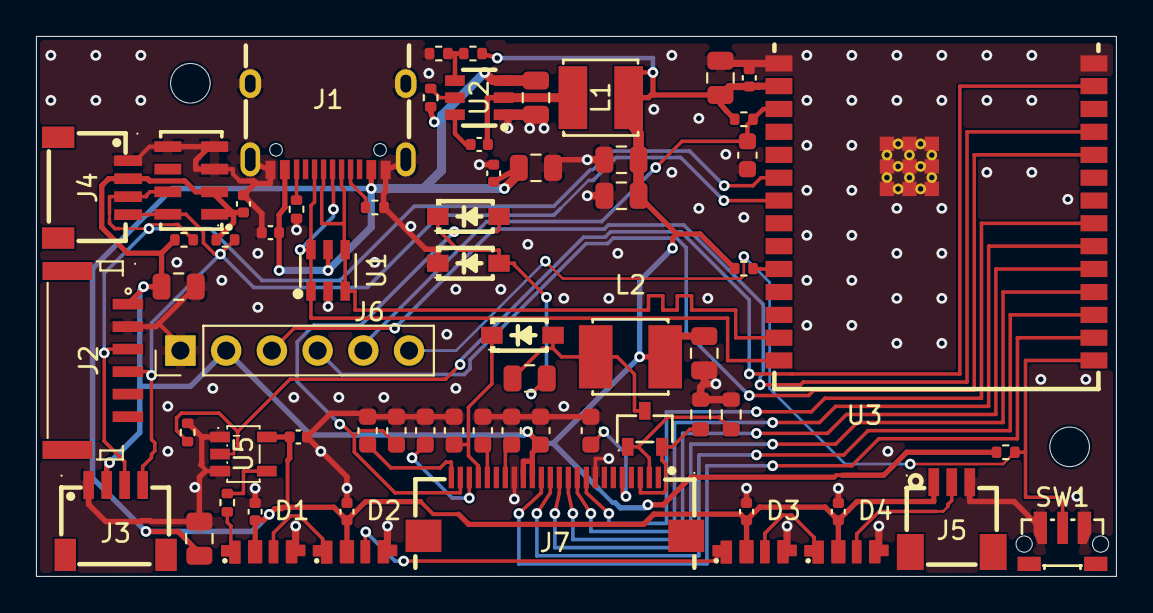
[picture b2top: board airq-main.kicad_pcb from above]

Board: 2 copper layers, 60.0 x 30.0 mm, 67 parts (0 on the bottom side), 42 nets.

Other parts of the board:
R14: 33R; R_0402_1005Metric

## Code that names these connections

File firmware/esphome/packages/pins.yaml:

# Mirrors hardware/interface.yaml (single source of truth). Keep in sync:
# tests/test_firmware_config.py::test_pins_mirror_interface enforces it.
substitutions:
  pin_i2c_sda: GPIO6
  pin_i2c_scl: GPIO7
  pin_epd_clk: GPIO19
  pin_epd_mosi: GPIO18
  pin_epd_cs: GPIO20
  pin_epd_dc: GPIO21
  pin_epd_rst: GPIO22
  pin_epd_busy: GPIO23
  pin_led_data: GPIO2
  pin_button: GPIO9
  pin_aux_uart_tx: GPIO16
  pin_aux_uart_rx: GPIO17
  addr_sen6x: "0x6B"
  addr_sht45: "0x44"
  addr_ms5611: "0x77"
  addr_veml7700: "0x10"
  addr_sfa40: "0x5D"

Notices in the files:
hardware/kicad/main/airq-main.kicad_pcb:
airQ open hardware (CC BY-SA 4.0)
